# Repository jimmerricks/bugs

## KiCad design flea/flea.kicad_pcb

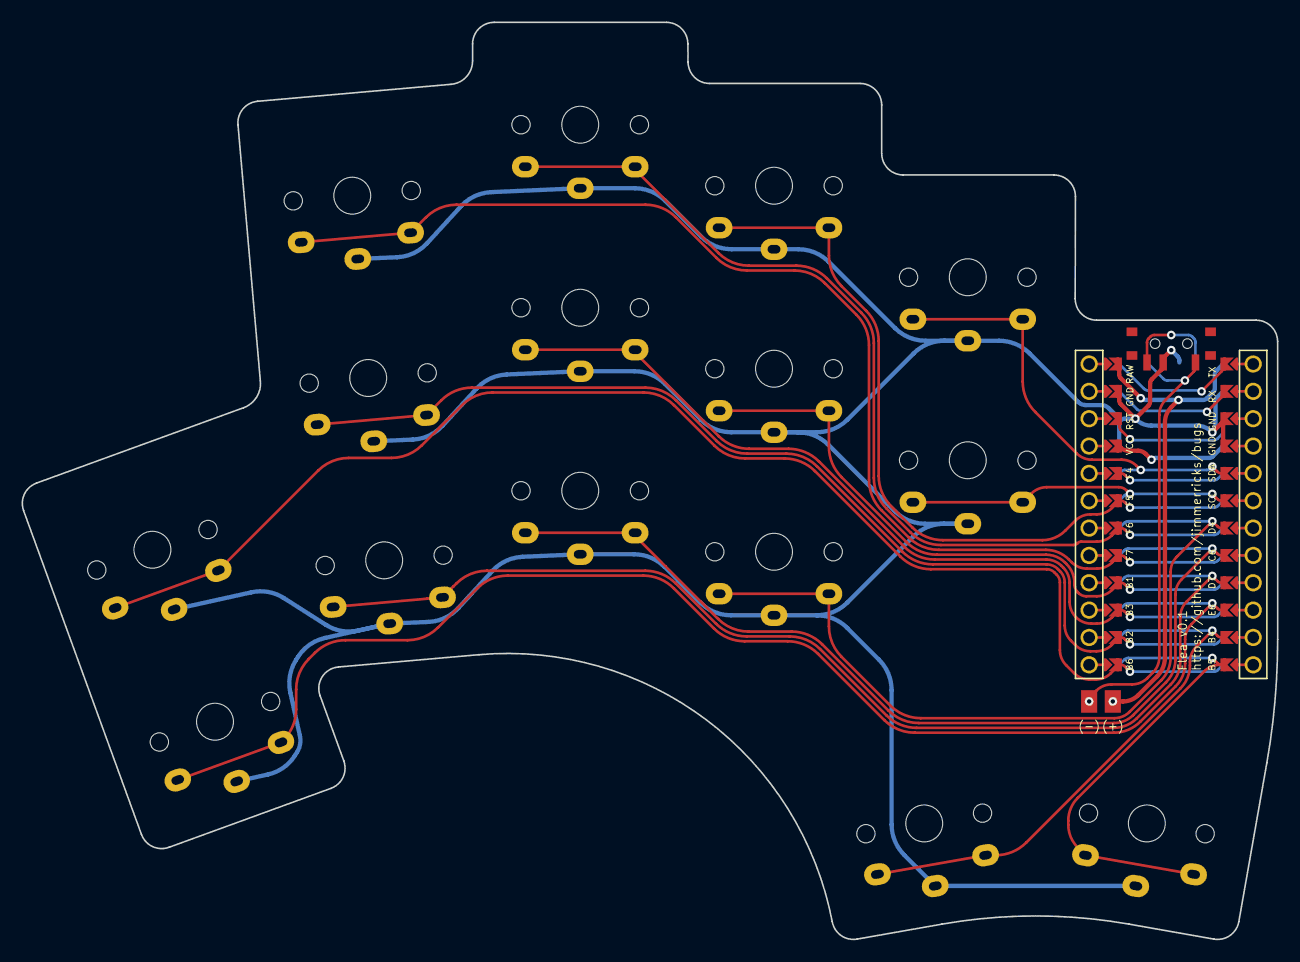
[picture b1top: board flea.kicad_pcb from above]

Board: 2 copper layers, 116.6 x 85.2 mm, 19 parts (1 on the bottom side), 18 nets.

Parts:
BT1: Battery_Cell; Battery_pads_reversible
PSW1: SW_SPDT; Power_reversible
Ref**: Val**; thread_m2
SW1, SW2, SW3, SW4, SW5, SW6, SW7, SW8, SW9, SW10, SW11, SW12, SW13, SW14, SW15: SW_PUSH; Choc_reversible
U1: ProMicro; ProMicro_jumpers

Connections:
GND: PSW1.2 (B), SW1.2, SW2.2, SW3.2, SW4.2, SW5.2, SW6.2, SW7.2, SW8.2, SW9.2, SW10.2, SW11.2, SW12.2, SW13.2, SW14.2, SW15.2, U1.3 (GND), U1.4 (GND), U1.23 (GND)
unnamed: BT1.2 (-), PSW1.1 (A)
raw: BT1.1 (+), U1.24 (RAW)
switch1: SW1.1, U1.17 (F7)
switch2: SW2.1, U1.18 (F6)
switch3: SW3.1, U1.19 (F5)
switch4: SW4.1, U1.5 (SDA)
switch5: SW5.1, U1.13 (B6)
switch6: SW6.1, U1.14 (B2)
switch7: SW7.1, U1.15 (B3)
switch8: SW8.1, U1.16 (B1)
switch9: SW9.1, U1.6 (SCL)
switch10: SW10.1, U1.10 (E6)
switch11: SW11.1, U1.9 (D7)
switch12: SW12.1, U1.8 (C6)
switch13: SW13.1, U1.7 (D4)
switch14: SW14.1, U1.11 (B4)
switch15: SW15.1, U1.12 (B5)

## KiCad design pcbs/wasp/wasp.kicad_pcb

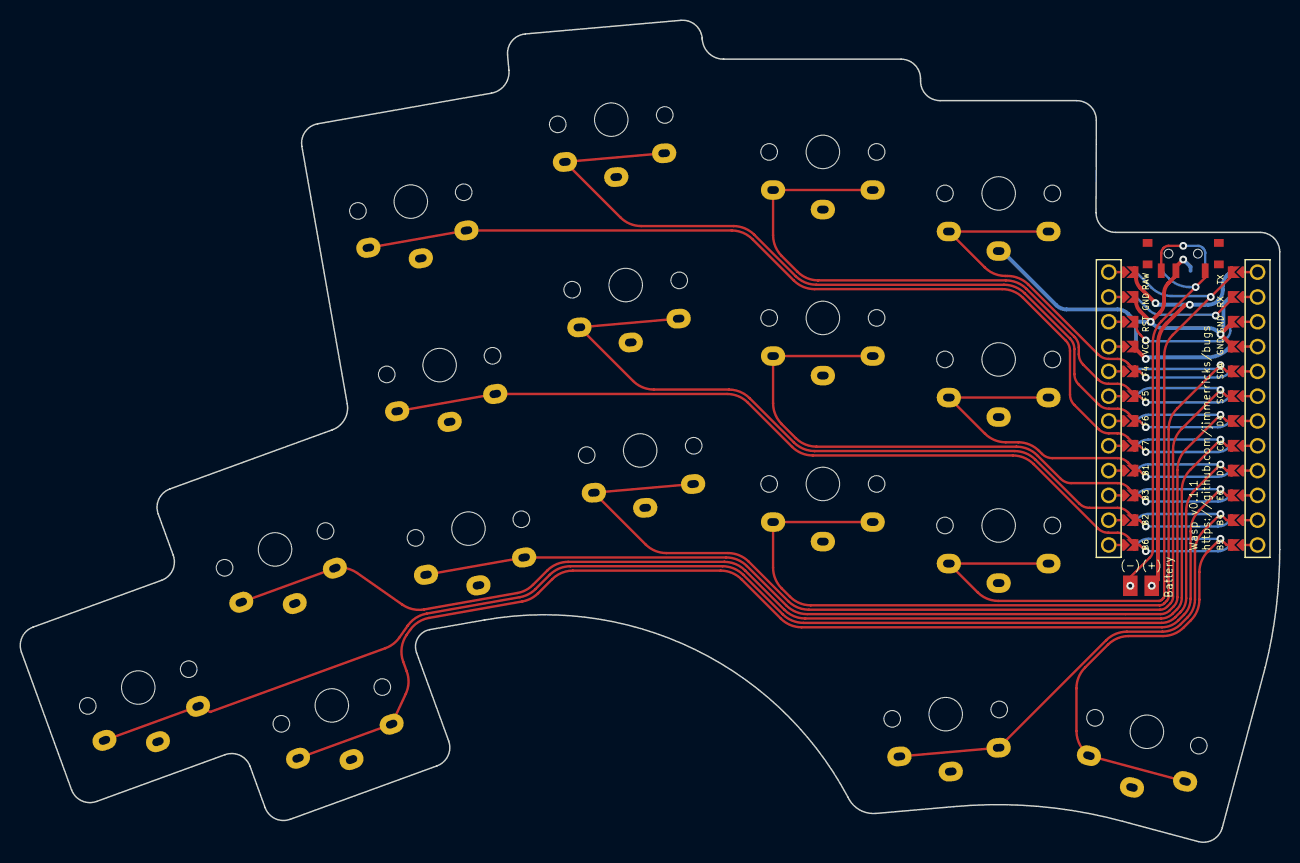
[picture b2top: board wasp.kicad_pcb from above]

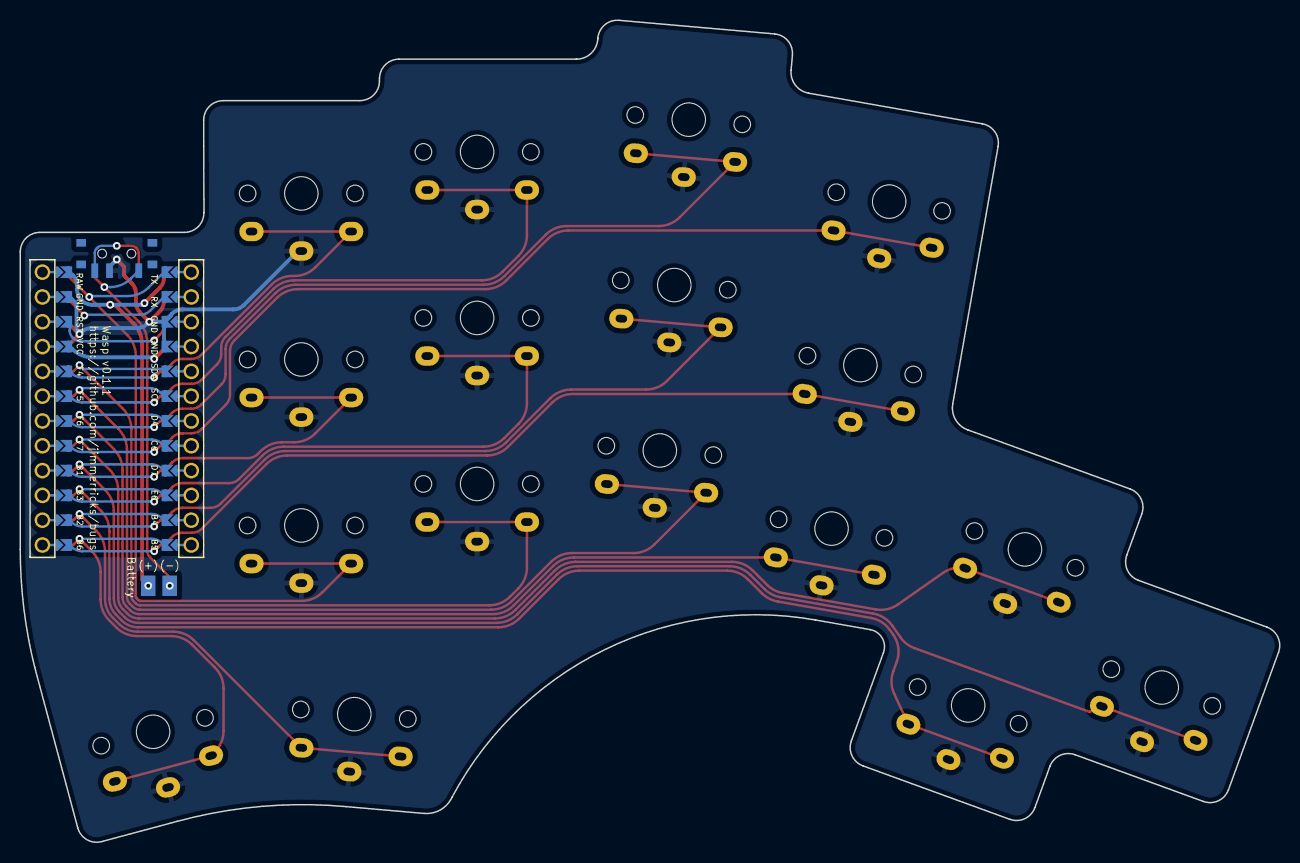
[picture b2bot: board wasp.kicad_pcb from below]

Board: 2 copper layers, 129.0 x 84.2 mm, 23 parts (3 on the bottom side), 20 nets.

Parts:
BT1: Battery_Cell; Battery_pads_reversible
PSW1: SW_SPDT; Power_reversible
Ref**: Val**; thread_m2
Ref**#2, Ref**#3: Val**; thread_m2
SW1, SW2, SW3, SW4, SW5, SW6, SW7, SW8, SW9, SW10, SW11, SW12, SW13, SW14, SW15, SW16, SW17: SW_PUSH; Choc_reversible
U1: ProMicro; ProMicro_jumpers

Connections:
GND: PSW1.2 (B), SW1.2, SW2.2, SW3.2, SW4.2, SW5.2, SW6.2, SW7.2, SW8.2, SW9.2, SW10.2, SW11.2, SW12.2, SW13.2, SW14.2, SW15.2, SW16.2, SW17.2, U1.3 (GND), U1.4 (GND), U1.23 (GND)
unnamed: BT1.2 (-), PSW1.1 (A)
raw: BT1.1 (+), U1.24 (RAW)
switch1: SW1.1, U1.9 (D7)
switch2: SW2.1, U1.17 (F7)
switch3: SW3.1, U1.18 (F6)
switch4: SW4.1, U1.19 (F5)
switch5: SW5.1, U1.20 (F4)
switch6: SW6.1, U1.8 (C6)
switch7: SW7.1, U1.13 (B6)
switch8: SW8.1, U1.14 (B2)
switch9: SW9.1, U1.15 (B3)
switch10: SW10.1, U1.16 (B1)
switch11: SW11.1, U1.10 (E6)
switch12: SW12.1, U1.7 (D4)
switch13: SW13.1, U1.6 (SCL)
switch14: SW14.1, U1.5 (SDA)
switch15: SW15.1, U1.1 (TX)
switch16: SW16.1, U1.11 (B4)
switch17: SW17.1, U1.12 (B5)
